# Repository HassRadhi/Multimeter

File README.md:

# Multimeter

DIY STM32F373 digital multimeter based on [MartinD OSM v1.5](https://github.com/MartinD-CZ/STM32F1-open-source-multimeter) — KiCad import, BOM, and firmware notes.

**Lab use only (±60 V / ±2.5 A). Not CAT-rated — do not use on mains.**

## Hardware

| Path | What |
|------|------|
| `hardware/v15.sch` / `.brd` / `.lbr` | Original Eagle 9.3 design |
| `hardware/V15_USB_isolator.*` | Optional USB isolator (Eagle) |
| `hardware/v15/` | KiCad import of the main meter (open `v15.kicad_pro`) |
| `hardware/schematics_sheet*.png` | Schematic previews |
| `hardware/v15_BOM.txt` | Upstream BOM |
| `hardware/DIGIKEY_PARTS.md` | Suggested DigiKey part links |
| `hardware/IMPORT_TO_KICAD.txt` | Eagle → KiCad import notes |

Upstream license terms apply to original files. See their repo `LICENSE` / file headers. Original additions in this repo are under the license in `LICENSE`.

## Next

1. Open `hardware/v15/v15.kicad_pro` in KiCad  
2. Run ERC / DRC  
3. Flash firmware from upstream `firmware-multimeter`

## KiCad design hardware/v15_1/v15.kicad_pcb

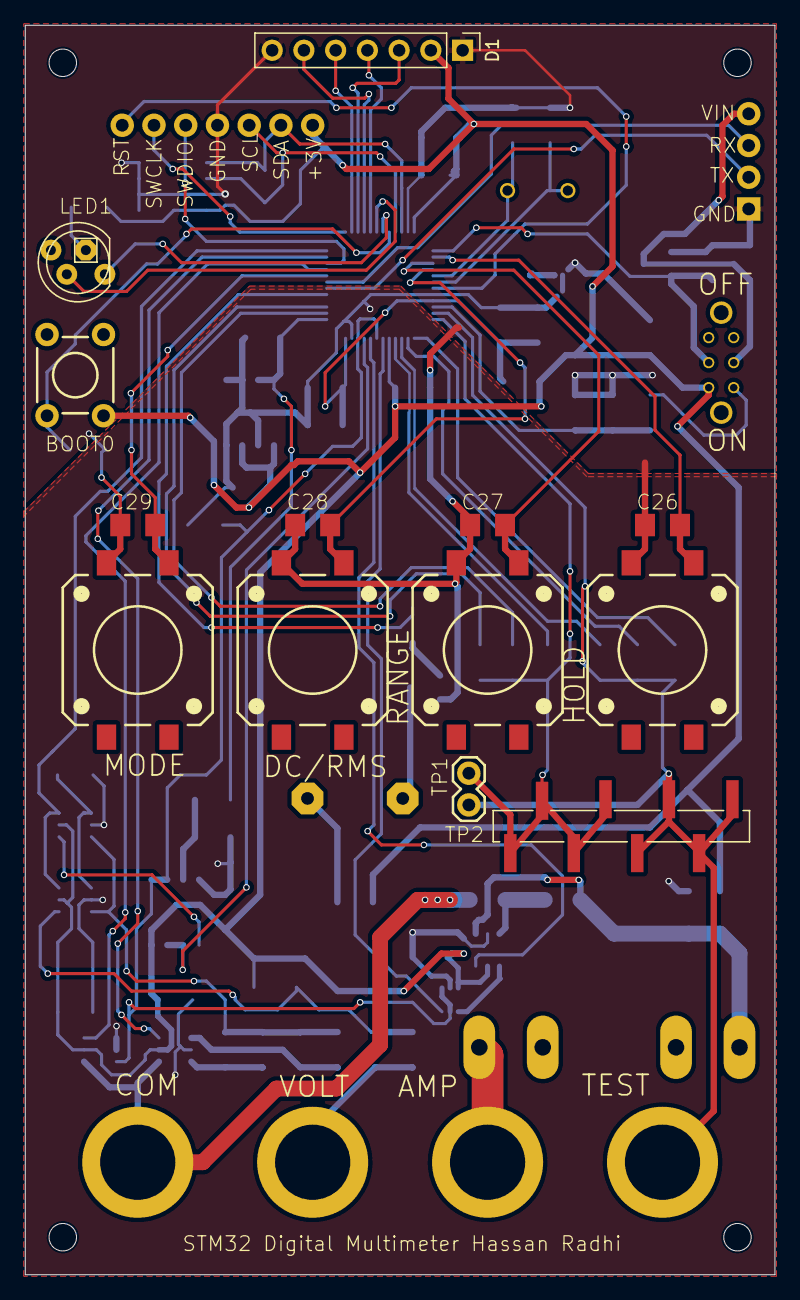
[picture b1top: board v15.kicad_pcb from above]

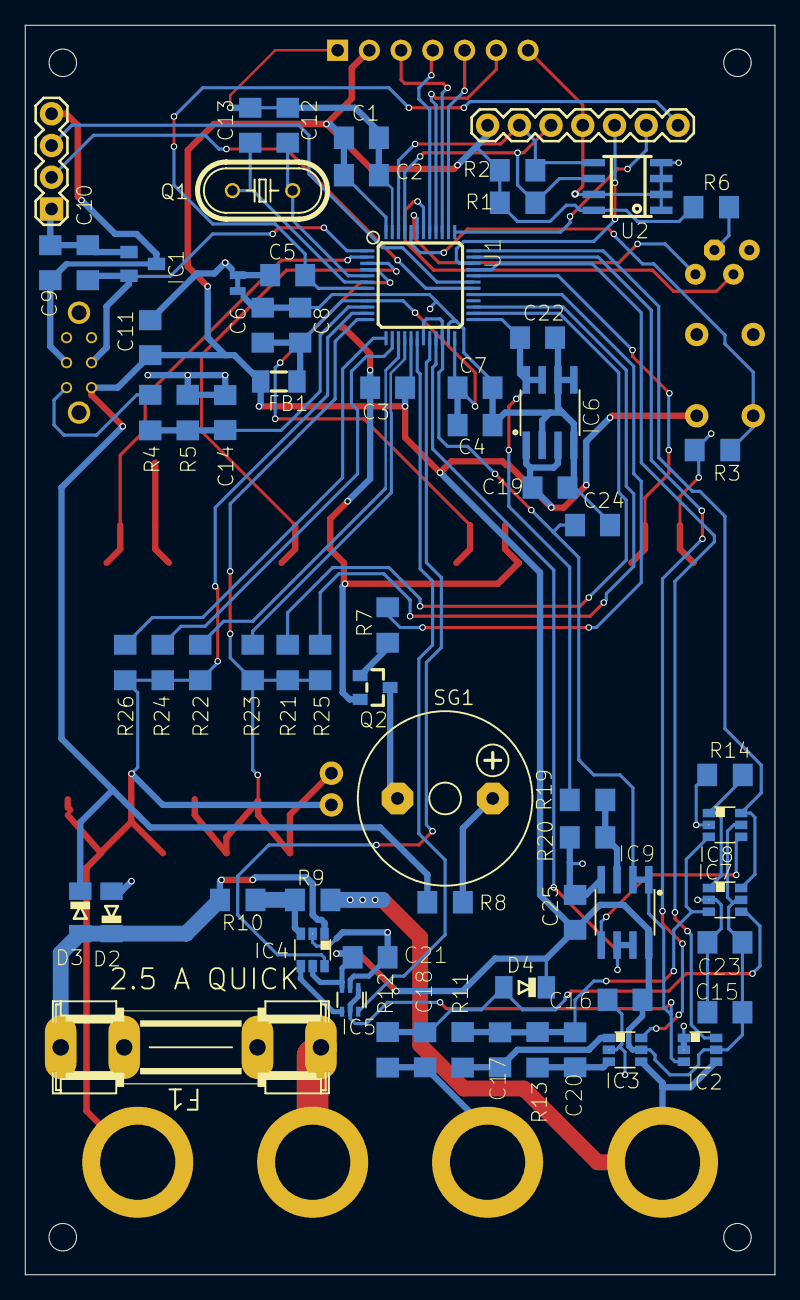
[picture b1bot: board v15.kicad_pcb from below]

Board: 2 copper layers, 60.0 x 100.0 mm, 90 parts (68 on the bottom side), 60 nets.

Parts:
C1, C9, C11: 22u; C1206
C2, C3, C5, C14, C19, C22, C24, C25, C26, C27, C28, C29: 100n; C1206
C4, C6, C10: 1u; C1206
C7, C8: 10n; C1206
C12, C13: 22p; C1206
C15, C16, C21, C23: 100n; 1206
C17, C18, C20: TBD; 1206
D1: SSD1306 128×64 SPI 7-pin; PinHeader_1x07_P2.54mm_Vertical
D2, D3, D4: DIODE-MINIMELF; MINIMELF
F1: 2.5 A QUICK; SHK20L
FB1: 1.8u; 1206
IC1: MCP1700; SOT23
IC2, IC3, IC4, IC7, IC8: 741G3157DBVR; DBV_R-PDSO-G6
IC5: INA199; SC70-6
IC6: MCP1501; SO08
IC9: MCP6072; SO08
LED1: RGBLED_CA-5MM; LED5MMRGB
P1, P2, P3, P4: BANANA_PLUG_PCB; BANANA_6MMHOLE
PT1: 2PT_GND_TIE
PWR0: M04PTH; 1X04@1
Q1: 8M; HC49U-V
Q2: 2N3904; SOT23
R1, R2, R23, R24: 2k2; R1206
R3, R4, R5: 10k; R1206
R6, R7, R19, R20: 1k; R1206
R8: 100; R1206
R9: 0R005; R1206
R10: 0R050; R1206
R11: 150k; R1206
R12: 1M; R1206
R13: 15k; R1206
R14: DNP; R1206
R21, R22: 220; R1206
R25, R26: 220k; R1206
S1: MOMENTARY-SWITCH-SPST-PTH-6.0MM; TACTILE_SWITCH_PTH_6.0MM
S2, S3, S4, S5: MOMENTARY-SWITCH-SPST-SMD-12MM; TACTILE_SWITCH_SMD_12MM
SG1: F/CM12P; F_CM12P
SW1: DPDT_SWITCH_SMALL; DPDT_SMALL
TP0: CONN_08SMD-STRAIGHT-FEMALE; 1X08_SMD
TPCON0: CONN_02; 1X02
U1: STM32F373CCT6; LQFP-48
U2: AT24C02; SOIC8
UNK_HOLE_0: dummyfp0
UNK_HOLE_1: dummyfp1
UNK_HOLE_2: dummyfp2
UNK_HOLE_3: dummyfp3

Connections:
3V: C1.1, C2.1, C3.1, C11.1, C15.1, C16.1, C19.1, C21.1, C23.1, C25.1, D1.2, D3.C, D4.C, FB1.1, IC2.5 (VCC), IC3.5 (VCC), IC4.5 (VCC), IC5.3 (V+), IC6.1 (VCC), IC6.3 (~SHDN), IC7.5 (VCC), IC8.5 (VCC), IC9.8 (V+), R1.1, R2.1, R6.1, R8.2, S1.3 (2), SW1.P$6 (NC2), U1.17 (VDD_17), U1.48 (VDD_48), U2.8 (VCC)
3V_STDBY: C10.1, IC1.2 (OUT), SW1.P$5 (I2), U1.1 (VBAT)
ADCI: IC5.6 (OUT), U1.18 (PB0)
ADCV: IC9.6 (-IN), IC9.7 (OUT), U1.21 (PE8)
ADC_VBAT: C14.1, R4.2, R5.1, U1.10 (PA0)
AGND: C4.2, C6.2, C7.2, C8.2, C15.2, C16.2, C19.2, C21.2, C22.2, C23.2, C24.2, C25.2, D2.A, IC2.1 (B), IC2.2 (GND), IC3.2 (GND), IC4.2 (GND), IC5.2 (GND), IC6.2 (GND0), IC6.4 (GND1), IC6.5 (GND2), IC6.6 (GND3), IC7.2 (GND), IC8.2 (GND), IC9.4 (V-), PT1.P$1, R14.1, R20.2, U1.8 (VSSA), U1.23 (VSSSD)
BOOT0: R3.1, S1.1, U1.44 (BOOT0)
BTN1: C29.1, S2.1, U1.32 (PA11)
BTN2: C28.1, S3.1, U1.4 (PC15)
BTN3: C27.1, S4.1, U1.3 (PC14)
BTN4: C26.1, S5.1, U1.2 (PC13)
BUZZ: R7.1, U1.29 (PA8)
GND: C1.2, C2.2, C3.2, C5.2, C9.2, C10.2, C11.2, C12.2, C13.2, C14.2, C26.2, C27.2, C28.2, C29.2, D1.1, D1.7, IC1.1 (GND), PT1.P$2, PWR0.1, Q2.2 (E), R3.2, R5.2, S2.3 (2), S3.3 (2), S4.3 (2), S5.3 (2), U1.47 (VSS_47), U2.1 (A0), U2.2 (A1), U2.3 (A2), U2.4 (GND), U2.7 (WP)
ISEL: IC4.6 (~A/B), U1.20 (PB2)
LCD_CLK: D1.3, U1.39 (PB3)
LCD_DC: D1.6, U1.40 (PB4)
LCD_DIN: D1.4, U1.41 (PB5)
LCD_RST: D1.5, U1.38 (PA15)
LEDG: LED1.3 (GREEN), U1.42 (PB6)
LEDR: LED1.1 (RED), U1.43 (PB7)
NRST: C5.1, U1.7 (NRST)
unnamed: F1.1A (1), P3.P$1 (1_P$1)
unnamed: D2.C, D3.A, F1.2A (2), IC4.1 (B), R10.1
unnamed: C9.1, IC1.3 (IN), PWR0.4, SW1.P$2 (I1)
unnamed: IC2.4 (X), IC3.4 (X), P1.P$1 (1_P$1), R9.2
unnamed: C20.1, IC3.3 (A), R13.2
unnamed: C17.1, IC3.1 (B), R11.2
unnamed: IC4.3 (A), R9.1, R10.2
unnamed: IC4.4 (X), IC5.4 (IN+)
unnamed: C17.2, C20.2, IC7.3 (A), IC8.3 (A), R11.1, R13.1
unnamed: IC7.1 (B), IC8.1 (B), R14.2
unnamed: C18.2, D4.A, IC7.4 (X), R12.2
unnamed: IC8.4 (X), IC9.5 (+IN)
unnamed: IC9.3 (+IN), R19.2, R20.1
unnamed: LED1.2 (VCC), R6.2
unnamed: C18.1, P2.P$1 (1_P$1), R12.1
unnamed: Q2.1 (B), R7.2
unnamed: Q2.3 (C), SG1.- (2)
unnamed: R8.1, SG1.+ (1)
unnamed: C12.1, Q1.1, U1.5 (PF0)
unnamed: C13.1, Q1.2, U1.6 (PF1)
unnamed: C4.1, C6.1, C7.1, C8.1, FB1.2, U1.9 (VDDA), U1.24 (VDDSD)
OFSEL: IC2.6 (~A/B), U1.33 (PA12)
RX: PWR0.3, U1.31 (PA10)
SCL: R1.2, U1.45 (PB8), U2.6 (SCL)
SDA: R2.2, U1.46 (PB9), U2.5 (SDA)
TP1A: R21.2, R23.2, R25.1, TP0.5, TP0.6, TP0.7, TP0.8, TPCON0.2, U1.12 (PA2)
TP1H: R25.2, U1.27 (PB15)
TP1L: R21.1, U1.26 (PB14)
TP1M: R23.1, U1.16 (PA6)
TP2A: P4.P$1 (1_P$1), R22.2, R24.2, R26.1, TP0.1, TP0.2, TP0.3, TP0.4, TPCON0.1, U1.11 (PA1)
TP2H: R26.2, U1.13 (PA3)
TP2L: R22.1, U1.15 (PA5)
TP2M: R24.1, U1.14 (PA4)
TX: PWR0.2, U1.30 (PA9)
VREF: C22.1, IC6.7 (OUT), IC6.8 (FB), R19.1, U1.25 (VREFSD+)
VREF/2: C24.1, IC2.3 (A), IC5.1 (REF), IC5.5 (IN-), IC9.1 (OUT), IC9.2 (-IN), U1.19 (PB1), U1.22 (PE9)
VSEL0: IC3.6 (~A/B), U1.35 (PF6)
VSEL1: IC7.6 (~A/B), IC8.6 (~A/B), U1.36 (PF7)
V_BATT: R4.1, SW1.P$1 (NC1)

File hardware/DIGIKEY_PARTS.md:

# DigiKey shopping list — STM32 OSM v1.5

Suggested MPNs for one board. DigiKey stock/pricing changes; open each link and confirm package matches the Eagle footprint before ordering.

**Search tip:** if a direct link fails, use  
`https://www.digikey.com/en/products/result?keywords=MPN`

## Critical ICs (order first)

| Ref | Suggested MPN | DigiKey search |
|-----|---------------|----------------|
| U1 | STM32F373CCT6 | https://www.digikey.com/en/products/result?keywords=STM32F373CCT6 |
| IC1 | MCP1700-3002E/TT (3.0 V LDO, SOT-23) | https://www.digikey.com/en/products/result?keywords=MCP1700-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 |
| IC2–IC4, IC7–IC8 (×5) | SN74LVC1G3157DBVR | https://www.digikey.com/en/products/detail/texas-instruments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 |
| IC5 | INA199A1DCKR *(gain 50 V/V — confirm vs firmware)* | https://www.digikey.com/en/products/result?keywords=INA199A1DCKR |
| IC6 | MCP1501-18E/SN (1.8 V ref, SOIC-8) | https://www.digikey.com/en/products/result?keywords=MCP1501-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 |
| IC9 | MCP6072-E/SN (dual op-amp SOIC-8) | https://www.digikey.com/en/products/result?keywords=MCP6072-E%2FSN |
| U2 | AT24C02D-SSHM-T or 24LC02B-I/SN | https://www.digikey.com/en/products/result?keywords=24LC02B-I%2FSN |
| Q2 | MMBT3904LT1G | https://www.digikey.com/en/products/result?keywords=MMBT3904LT1G |

## Passives & discretes

| Ref / qty | Value | DigiKey search (1206 unless noted) |
|-----------|-------|-------------------------------------|
| C× many | 100 nF 50 V X7R 1206 | https://www.digikey.com/en/products/result?keywords=1206+100nF+X7R |
| C1,C9,C11 | 22 µF 16 V 1206 | https://www.digikey.com/en/products/result?keywords=1206+22uF+16V |
| C4,C6,C10 | 1 µF 16 V 1206 | https://www.digikey.com/en/products/result?keywords=1206+1uF+X7R |
| C7,C8 | 10 nF 50 V 1206 | https://www.digikey.com/en/products/result?keywords=1206+10nF |
| C12,C13 | 22 pF C0G 1206 | https://www.digikey.com/en/products/result?keywords=1206+22pF+C0G |
| C17,C18,C20 | **TBD on schematic** — start with 100 nF C0G/X7R 1206 until you tune | same 100 nF link |
| R1,R2 | 2.2 kΩ 1% 1206 | https://www.digikey.com/en/products/result?keywords=1206+2.2k+1%25 |
| R3–R5 | 10 kΩ 1% 1206 | https://www.digikey.com/en/products/result?keywords=1206+10k+1%25 |
| R6,R7,R19,R20 | 1 kΩ 1% 1206 | https://www.digikey.com/en/products/result?keywords=1206+1k+1%25 |
| R8 | 100 Ω 1% 1206 | https://www.digikey.com/en/products/result?keywords=1206+100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 |
| R9 | **5 mΩ** shunt (0R005), ≥1 W class | https://www.digikey.com/en/products/result?keywords=5+mOhm+s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 |
| R10 | **50 mΩ** shunt (0R050) | https://www.digikey.com/en/products/result?keywords=50+mOhm+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 |
| R11 | 150 kΩ 0.1%/1% 1206 | https://www.digikey.com/en/products/result?keywords=1206+150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 |
| R12 | 1 MΩ 0.1%/1% 1206 | https://www.digikey.com/en/products/result?keywords=1206+1M+0.1%25 |
| R13 | 15 kΩ 0.1%/1% 1206 | https://www.digikey.com/en/products/result?keywords=1206+15k+0.1%25 |
| R14 | **DNP** — do not buy | — |
| R21,R22 | 220 Ω | https://www.digikey.com/en/products/result?keywords=1206+220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 |
| R23,R24 | 2.2 kΩ | (same as R1) |
| R25,R26 | 220 kΩ | https://www.digikey.com/en/products/result?keywords=1206+220k+1%25 |
| FB1 | Ferrite bead ~1.8 µH / 1206 | https://www.digikey.com/en/products/result?keywords=1206+fer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 |
| D2–D4 | SOD-80 / MiniMELF switching diode (e.g. LL4148) | https://www.digikey.com/en/products/result?keywords=LL4148 |
| Q1 | 8 MHz HC-49/U crystal | https://www.digikey.com/en/products/result?keywords=8MHz+HC-49 |
| F1 | 2.5 A fast fuse (match SHK20L footprint / holder) | https://www.digikey.com/en/products/result?keywords=2.5A+fas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 |

## Connectors / UI / mech

| Ref | What | DigiKey search |
|-----|------|----------------|
| D1 | Nokia 5110 / PCD8544 LCD module | **not DigiKey** — AliExpress / Adafruit-style “Nokia 5110” |
| P1–P4 | PCB banana jack 4 mm | https://www.digikey.com/en/products/result?keywords=banana+j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 |
| S1 | 6 mm tactile PTH | https://www.digikey.com/en/products/result?keywords=tactile+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 |
| S2–S5 | 12 mm SMD tactile | https://www.digikey.com/en/products/result?keywords=tactile+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 |
| SW1 | small DPDT slide | https://www.digikey.com/en/products/result?keywords=DPDT+sli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 |
| LED1 | 5 mm RGB common-anode | https://www.digikey.com/en/products/result?keywords=RGB+LED+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 |
| SG1 | magnetic buzzer ~3 V | https://www.digikey.com/en/products/result?keywords=magnetic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 |
| EXP / PWR / TP | 2.54 mm pin headers | https://www.digikey.com/en/products/result?keywords=pin+head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 |

## Also needed (not on main BOM)

- PCB fab from `v15.brd` (JLCPCB etc.) after Gerber export  
- Optional: `V15_USB_isolator` board + isolator parts  
- LiPo / battery holder, probes, 3D-printed case  
- ST-Link (or use SWD on EXP header) for programming  

## Before you click Buy

1. Confirm **INA199** gain (A1/A2/A3) against firmware.  
2. Confirm **MCP1700** is **3.0 V** version (`-3002`).  
3. Confirm **MCP1501** is **1.8 V** (`-18`).  
4. Fill **C17/C18/C20** (author left TBD).  
5. Skip **R14**.  
6. Match shunt packages to the Eagle footprints (power rating!).
